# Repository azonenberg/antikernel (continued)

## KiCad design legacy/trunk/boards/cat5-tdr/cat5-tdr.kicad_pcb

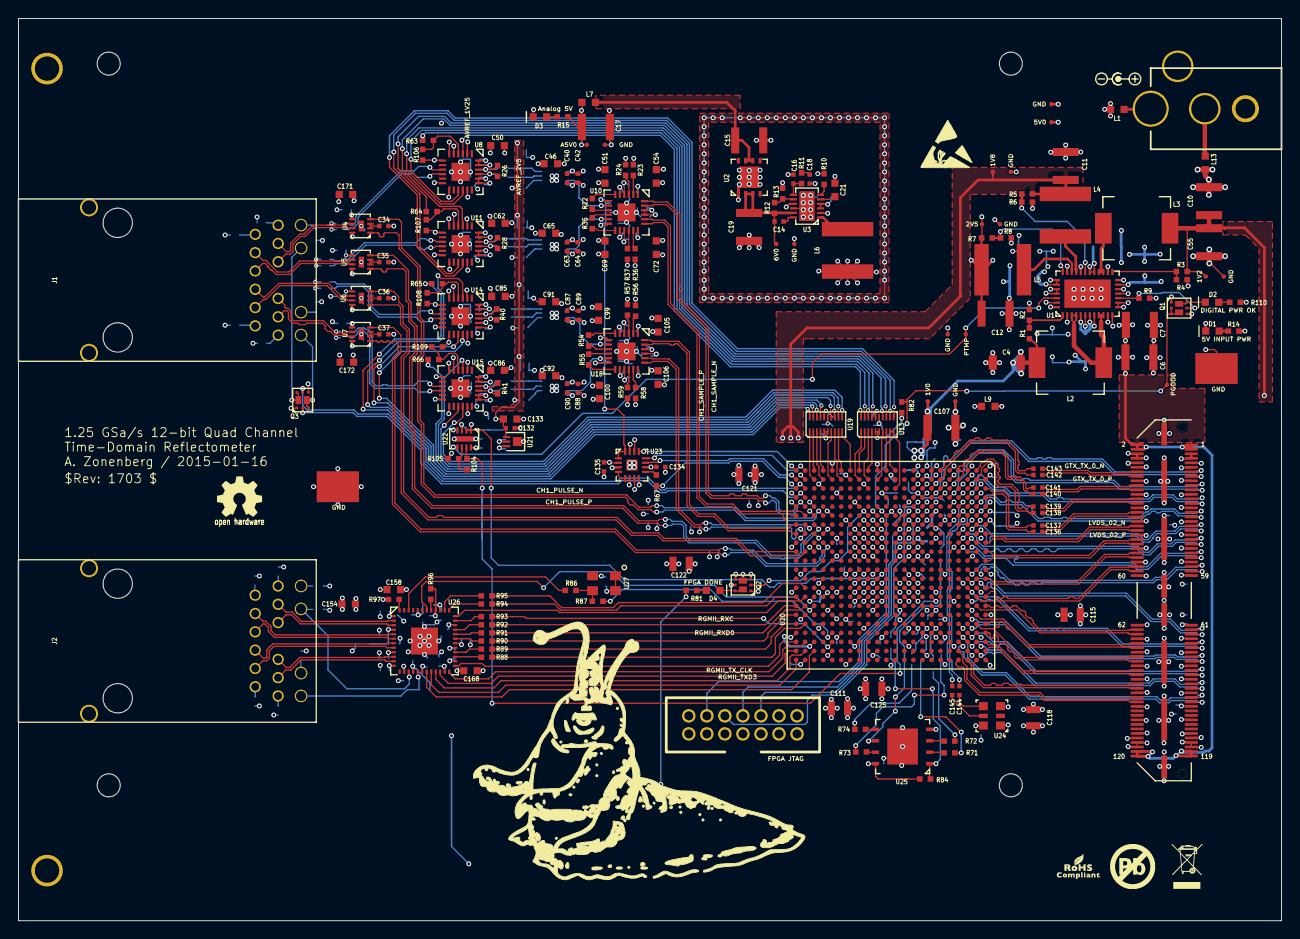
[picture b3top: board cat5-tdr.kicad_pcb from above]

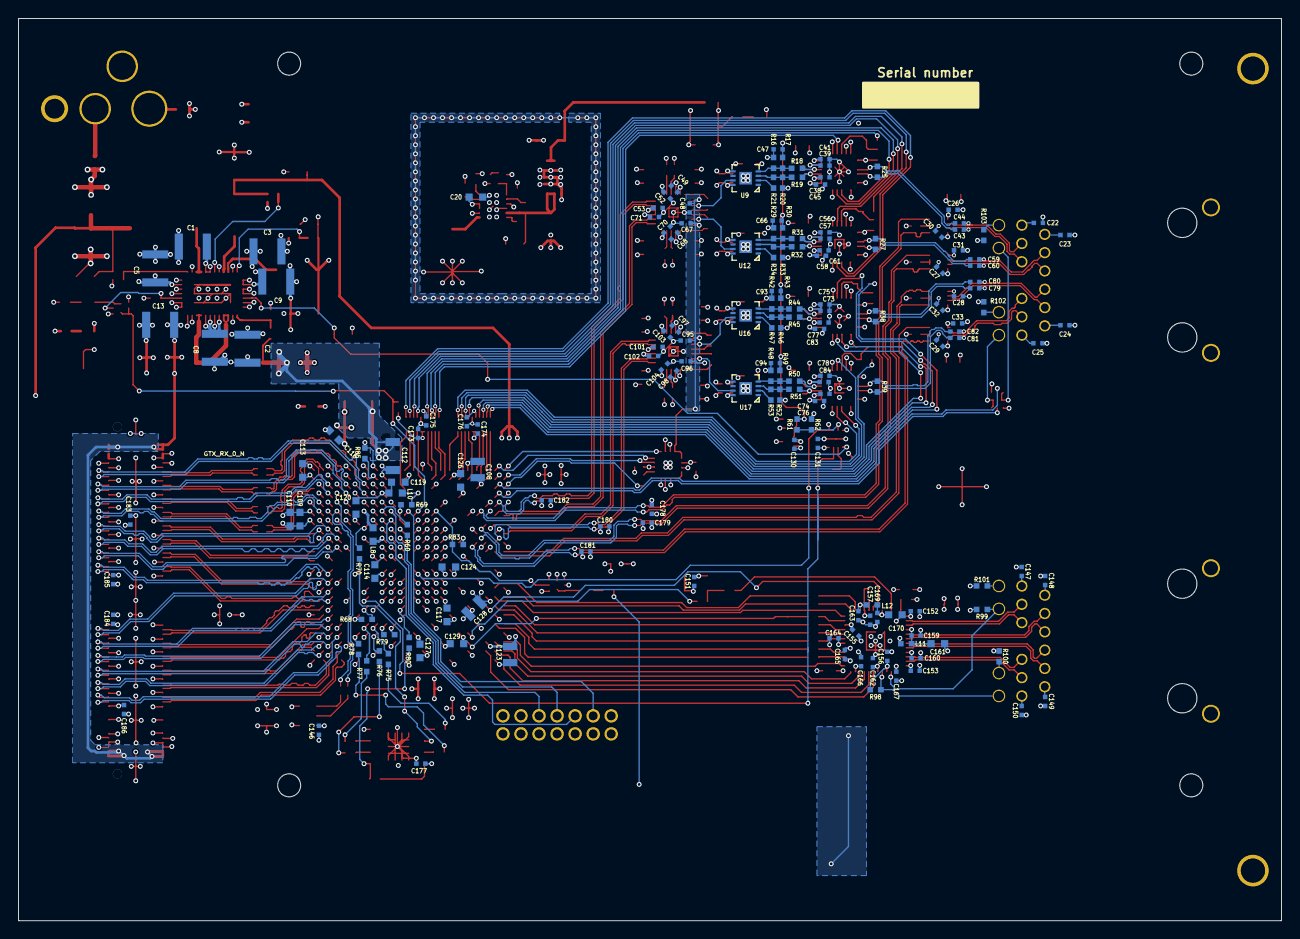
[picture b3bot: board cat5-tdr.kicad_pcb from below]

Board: 4 copper layers, 140.0 x 100.0 mm, 372 parts (174 on the bottom side), 313 nets.

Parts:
C1, C2, C3, C5, C6, C7, C8, C9, C10, C11, C12, C13, C15, C17, C19, C55: 22 uF; EIA_1210_CAP_NOSILK
C4, C112: 100 uF; EIA_1206_CAP_NOSILK
C14, C22, C23, C24, C25, C26, C27, C28, C29, C38, C39, C40, C41, C42, C43, C44, C45, C47, C48, C49, C52, C53, C56, C57, C58, C59, C60, C61, C63, C64, C66, C67, C68, C70, C71, C73, C74, C75, C76, C77, C78, C79, C80, C81, C82, C83, C84, C87, C88, C89, C90, C93, C94, C95, C96, C97, C98, C101, C102, C103, C104, C130, C131, C132, C134, C135, C136, C137, C138, C139, C140, C141, C142, C143, C144, C145, C146, C147, C148, C149, C150, C151, C152, C153, C155, C156, C157, C159, C160, C162, C163, C164, C165, C166, C167, C169, C173, C174, C175, C176, C177, C178, C179, C180, C181, C182, C183, C184, C185, C186: 0.1 uF; EIA_0402_CAP_NOSILK
C16: 10 pF; EIA_0402_CAP_NOSILK
C18: 390 pF; EIA_0402_CAP_NOSILK
C20, C21, C46, C50, C51, C54, C62, C65, C69, C72, C85, C86, C91, C92, C99, C100, C105, C106, C109, C110, C113, C114, C116, C117, C119, C120, C124, C126, C127, C129, C133, C154, C158, C161, C168, C170, C171, C172: 4.7 uF; EIA_0603_CAP_NOSILK
C30, C31, C32, C33, C34, C35, C36, C37: 10 nF; EIA_0402_CAP_NOSILK
C107: 330 uF; EIA_1210_CAP_NOSILK
C108, C111, C115, C118, C121, C122, C123, C125, C128: 47 uF; EIA_0805_CAP_NOSILK
D1, D2, D3, D4: GREEN; EIA_0603_LED
J1, J2: BEL_FUSE_0826-1G1T-23-F; CONN_BELFUSE_0826_1G1T_23_F
J3: XILINX_JTAG; XILINX_JTAG_PTH_MOLEX_0878311420
J4: QTH_060_01_L_D_A_ZMCPINOUT; CONN_SAMTEC_QTH-060-01-L-D-A
K1: BARREL_JACK; CONN_CUI_PJ-058BH_HIPWR_BARREL_NOSLOT
L1, L7, L8, L9, L10, L13: TDK MPZ1608S101ATAH0; EIA_0603_INDUCTOR_NOSILK
L2, L3: 2.2 uH 8.2A; INDUCTOR_TDK_SPM6530
L4, L5: 2.2 uH 3.7A; INDUCTOR_YUDEN_NR6028
L6: 3 uH 3.2A; INDUCTOR_YUDEN_NR6028
L11, L12: 600R; EIA_0402_RES_NOSILK
MECHANICAL_EUROCARD_3U_FRONTHOLES: VAL**; MECHANICAL_EUROCARD_3U_FRONTHOLES
Q1, Q2, Q3: SSM6N58NU; DFN_6_0.65MM_2x2MM_GDS
R1: 255K; EIA_0402_RES_NOSILK
R2, R7: 1.02M; EIA_0402_RES_NOSILK
R3: 232K; EIA_0402_RES_NOSILK
R4: 464K; EIA_0402_RES_NOSILK
R5: 806K; EIA_0402_RES_NOSILK
R6: 649K; EIA_0402_RES_NOSILK
R8: 475K; EIA_0402_RES_NOSILK
R9, R79, R96, R99: 1K; EIA_0402_RES_NOSILK
R10: 28.7K; EIA_0402_RES_NOSILK
R11: 210K; EIA_0402_RES_NOSILK
R12: 820K; EIA_0402_RES_NOSILK
R13: 205K; EIA_0402_RES_NOSILK
R14, R15, R110: 470; EIA_0402_RES_NOSILK
R16, R17, R18, R19, R20, R21, R23, R24, R29, R30, R31, R32, R33, R34, R36, R37, R42, R43, R44, R45, R46, R47, R48, R49, R50, R51, R52, R53, R56, R57, R58, R59, R61, R62, R105: 100K; EIA_0402_RES_NOSILK
R22, R35, R54, R55: 20K; EIA_0402_RES_NOSILK
R25, R26, R27, R28, R38, R39, R40, R41: 100; EIA_0402_RES_NOSILK
R60, R63, R64, R65, R66, R67, R70, R71, R72, R73, R74, R75, R76, R77, R78, R80, R86, R87, R88, R89, R90, R91, R92, R93, R94, R95: 49.9; EIA_0402_RES_NOSILK
R68: 0; EIA_0402_RES_NOSILK
R69, R82: 4.7K; EIA_0402_RES_NOSILK
R81, R100, R101, R102, R103: 220; EIA_0402_RES_NOSILK
R83: 330; EIA_0402_RES_NOSILK
R84: 2.4K; EIA_0402_RES_NOSILK
R85: 100R 1%; EIA_0402_RES_NOSILK
R97: 12.1K 1%; EIA_0402_RES_NOSILK
R98: 10K; EIA_0402_RES_NOSILK
R104: 200K; EIA_0402_RES_NOSILK
R106, R107, R108, R109: 240; EIA_0402_RES_NOSILK
STENCIL8_TOOLING_HOLE, STENCIL8_TOOLING_HOLE#2, STENCIL8_TOOLING_HOLE#3, STENCIL8_TOOLING_HOLE#4: VAL**; STENCIL8_TOOLING_HOLE
TP1, TP2, TP3, TP4, TP5, TP6, TP7, TP8, TP9, TP10, TP11, TP12, TP13, TP14, TP15, TP16, TP17: CONN_1; TESTPOINT_SMT_0.5MM
TP18, TP19: CONN_1; TESTPOINT_SMT_KEYSTONE_5016
U1: LTC3374-QFN; QFN_38_0.5MM_5x7MM
U2: NCP59150MN50; DFN_8_0.8MM_4x4MM
U3: LTC3122; DFN_12_0.5MM_3x4MM
U4, U5, U6, U7: SY58603U; DFN_8_0.5MM_2x2MM
U8, U11, U14, U15: LMH6881; QFN_24_0.5MM_4x4MM
U9, U12, U16, U17: AD8045; DFN_8_0.5MM_3x3MM
U10, U18: LMH7322; QFN_24_0.5MM_4x4MM
U13, U19: TXB0108DQS; DFN_20_0.4MM_2x4MM
U20: XC7K70T-1FBG484; BGA_484_22x22_FULLARRAY_1MM
U21: LT6660 2.5V; DFN_3_0.5MM_2x2MM
U22: MCP6402-DFN; DFN_8_0.5MM_2x3MM
U23: DAC7752; QFN_16_0.5MM_3x3MM
U24: 125 MHz; OSCILLATOR_LVDS_3.2x2.5
U25: MX25U6435FZNI-10G; DFN_8_1.27MM_6x5MM
U26: KSZ9031RN; QFN_48_0.5MM_7x7MM
U27: 25 MHz; OSCILLATOR_3.2x2.5

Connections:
/Analog Front End/1V8: C11.1, C108.1, C111.1, C121.1, C122.1, C123.1, C124.1, C125.1, C126.1, C127.1, C128.1, C129.1, C134.2, C151.1, C155.1, C156.1, C157.1, C158.1, C173.1, C174.1, C177.2, C178.1, C179.1, C180.1, C181.1, C182.1, J3.2, L4.1, L10.2, R5.1, R69.1, R82.2, R83.2, R84.1, R96.1, R98.1, TP7.1, U13.5, U13.6, U19.5, U19.6, U20.AA7, U20.AA17, U20.AB4, U20.AB14, U20.F22, U20.G19, U20.H7, U20.J7, U20.K10, U20.K12, U20.K20, U20.L17, U20.M4, U20.M10, U20.N1, U20.N7, U20.N21, U20.P7, U20.P8, U20.P10, U20.P12, U20.P18, U20.R5, U20.R9, U20.R11, U20.T2, U20.T12, U20.T22, U20.U9, U20.U19, U20.V6, U20.V16, U20.W3, U20.W13, U20.Y10, U20.Y20, U23.7, U23.10, U23.14, U25.8, U26.16, U26.34, U26.40, U27.1, U27.4
/Analog Front End/2V5: C12.1, C26.1, C27.1, C28.1, C29.1, C30.1, C31.1, C32.1, C33.1, C52.1, C53.1, C54.1, C70.1, C71.1, C72.1, C101.1, C102.1, C103.1, C104.1, C105.1, C106.1, C115.1, C118.1, C146.1, C152.1, C153.1, C154.1, C171.1, C172.1, C175.1, C176.1, C183.1, C184.1, C185.1, C186.1, J4.9, J4.10, J4.111, J4.112, L5.1, R7.1, R24.1, R37.1, R57.1, R59.1, R81.1, R100.2, R101.2, R102.1, R103.1, TP9.1, U4.8, U5.8, U6.8, U7.8, U10.1, U10.18, U10.21, U10.22, U13.16, U18.1, U18.18, U18.21, U18.22, U19.16, U20.A17, U20.B14, U20.C11, U20.C21, U20.D8, U20.D18, U20.E15, U20.F12, U20.G9, U20.H16, U24.1, U24.6, U26.1, U26.12
/Analog Front End/A5V0: C17.1, C38.1, C39.1, C40.1, C41.1, C42.1, C45.1, C46.1, C49.1, C50.1, C51.1, C56.1, C57.1, C58.1, C61.1, C62.1, C63.1, C64.1, C65.1, C68.1, C69.1, C73.1, C74.1, C75.1, C76.1, C77.1, C78.1, C83.1, C84.1, C85.1, C86.1, C87.1, C88.1, C89.1, C90.1, C91.1, C92.1, C97.1, C98.1, C99.1, C100.1, C130.1, C131.1, C135.2, L7.1, R15.2, TP13.1, U8.5, U8.19, U8.20, U8.23, U8.24, U9.8, U10.5, U10.14, U11.5, U11.19, U11.20, U11.23, U11.24, U12.8, U14.5, U14.19, U14.20, U14.23, U14.24, U15.5, U15.19, U15.20, U15.23, U15.24, U16.8, U17.8, U18.5, U18.14, U21.3, U22.8, U23.2, U23.6, U23.15
/Analog Front End/AFE_VREF: C48.1, C67.1, C95.1, C96.1, U10.7, U10.12, U18.7, U18.12, U23.1, U23.16
/Analog Front End/AVREF_1V25: U8.2, U11.2, U14.2, U15.2, U20.M12, U22.1, U22.2
/Analog Front End/AVREF_1V25_UNBUF: R61.2, R62.1, U22.3
/Analog Front End/AVREF_2V5: C47.1, C66.1, C93.1, C94.1, C132.1, C133.1, R17.2, R30.2, R43.2, R49.2, R61.1, U21.1
/Analog Front End/CAT5_CH1_N: C44.1, J1.11, U4.6
/Analog Front End/CAT5_CH1_P: C43.1, J1.10, U4.7
/Analog Front End/CAT5_CH2_N: C60.1, J1.5, U5.6
/Analog Front End/CAT5_CH2_P: C59.1, J1.4, U5.7
/Analog Front End/CAT5_CH3_N: C80.1, J1.3, U6.6
/Analog Front End/CAT5_CH3_P: C79.1, J1.2, U6.7
/Analog Front End/CAT5_CH4_N: C82.1, J1.9, U7.6
/Analog Front End/CAT5_CH4_P: C81.1, J1.8, U7.7
/Analog Front End/CH1_AC_N: C44.2, R25.2, U8.9
/Analog Front End/CH1_AC_P: C43.2, R25.1, U8.10
/Analog Front End/CH1_BUF_N: R19.2, R26.2, U8.21
/Analog Front End/CH1_BUF_P: R18.2, R26.1, U8.22
/Analog Front End/CH1_SAMPLE_N: U10.24, U20.AB5
/Analog Front End/CH1_SAMPLE_P: U10.23, U20.AA5
/Analog Front End/CH1_SPI_CS_N: U8.16, U13.17
/Analog Front End/CH1_SPI_MISO: R63.2, R106.2, U8.4
/Analog Front End/CH1_SPI_MOSI: U8.3, U13.20
/Analog Front End/CH1_SPI_SCK: U8.15, U13.18
/Analog Front End/CH1_VDIFF: U9.7, U10.8
/Analog Front End/CH2_AC_N: C60.2, R27.2, U11.9
/Analog Front End/CH2_AC_P: C59.2, R27.1, U11.10
/Analog Front End/CH2_BUF_N: R28.2, R32.2, U11.21
/Analog Front End/CH2_BUF_P: R28.1, R31.2, U11.22
/Analog Front End/CH2_SAMPLE_N: U10.19, U20.AB6
/Analog Front End/CH2_SAMPLE_P: U10.20, U20.AA6
/Analog Front End/CH2_SPI_CS_N: U11.16, U13.11
/Analog Front End/CH2_SPI_MISO: R64.2, R107.2, U11.4
/Analog Front End/CH2_SPI_MOSI: U11.3, U13.14
/Analog Front End/CH2_SPI_SCK: U11.15, U13.12
/Analog Front End/CH2_VDIFF: U10.11, U12.7
/Analog Front End/CH3_AC_N: C80.2, R38.2, U14.9
/Analog Front End/CH3_AC_P: C79.2, R38.1, U14.10
/Analog Front End/CH3_BUF_N: R40.2, R45.2, U14.21
/Analog Front End/CH3_BUF_P: R40.1, R44.2, U14.22
/Analog Front End/CH3_SAMPLE_N: U18.24, U20.AB7
/Analog Front End/CH3_SAMPLE_P: U18.23, U20.AB8
/Analog Front End/CH3_SPI_CS_N: U14.16, U19.17
/Analog Front End/CH3_SPI_MISO: R65.2, R108.2, U14.4
/Analog Front End/CH3_SPI_MOSI: U14.3, U19.19
/Analog Front End/CH3_SPI_SCK: U14.15, U19.18
/Analog Front End/CH3_VDIFF: U16.7, U18.8
/Analog Front End/CH4_AC_N: C82.2, R39.2, U15.9
/Analog Front End/CH4_AC_P: C81.2, R39.1, U15.10
/Analog Front End/CH4_BUF_N: R41.2, R51.2, U15.21
/Analog Front End/CH4_BUF_P: R41.1, R50.2, U15.22
/Analog Front End/CH4_SAMPLE_N: U18.19, U20.AA8
/Analog Front End/CH4_SAMPLE_P: U18.20, U20.AA9
/Analog Front End/CH4_SPI_CS_N: U15.16, U19.11
/Analog Front End/CH4_SPI_MISO: R66.2, R109.2, U15.4
/Analog Front End/CH4_SPI_MOSI: U15.3, U19.13
/Analog Front End/CH4_SPI_SCK: U15.15, U19.12
/Analog Front End/CH4_VDIFF: U17.7, U18.11
/Analog Front End/DAC_SPI_CS_N: U20.AB2, U23.11
/Analog Front End/DAC_SPI_MISO: R67.2, U23.9
/Analog Front End/DAC_SPI_MOSI: U20.AB1, U23.13
/Analog Front End/DAC_SPI_SCK: U20.AA1, U23.12
/Analog Front End/GND: C1.2, C2.2, C3.2, C4.2, C5.2, C6.2, C7.2, C8.2, C9.2, C10.2, C11.2, C12.2, C13.2, C15.2, C16.2, C17.2, C18.2, C19.2, C20.2, C21.2, C22.2, C23.2, C24.2, C25.2, C26.2, C27.2, C28.2, C29.2, C30.2, C31.2, C32.2, C33.2, C34.2, C35.2, C36.2, C37.2, C38.2, C39.2, C40.2, C41.2, C42.2, C45.2, C46.2, C47.2, C48.2, C49.2, C50.2, C51.2, C52.2, C53.2, C54.2, C55.2, C56.2, C57.2, C58.2, C61.2, C62.2, C63.2, C64.2, C65.2, C66.2, C67.2, C68.2, C69.2, C70.2, C71.2, C72.2, C73.2, C74.2, C75.2, C76.2, C77.2, C78.2, C83.2, C84.2, C85.2, C86.2, C87.2, C88.2, C89.2, C90.2, C91.2, C92.2, C93.2, C94.2, C95.2, C96.2, C97.2, C98.2, C99.2, C100.2, C101.2, C102.2, C103.2, C104.2, C105.2, C106.2, C107.2, C108.2, C109.2, C110.2, C111.2, C112.2, C113.2, C114.2, C115.2, C116.2, C117.2, C118.2, C119.2, C120.2, C121.2, C122.2, C123.2, C124.2, C125.2, C126.2, C127.2, C128.2, C129.2, C130.2, C131.2, C132.2, C133.2, C134.1, C135.1, C146.2, C147.2, C148.2, C149.2, C150.2, C151.2, C152.2, C153.2, C154.2, C155.2, C156.2, C157.2, C158.2, C159.2, C160.2, C161.2, C162.2, C163.2, C164.2, C165.2, C166.2, C167.2, C168.2, C169.2, C170.2, C171.2, C172.2, C173.2, C174.2, C175.2, C176.2, C177.1, C178.2, C179.2, C180.2, C181.2, C182.2, C183.2, C184.2, C185.2, C186.2, D1.2, D3.2, J1.17, J2.17, J3.3, J3.5, J3.7, J3.9, J3.11, J4.5, J4.6, J4.7, J4.8, J4.11, J4.12, J4.17, J4.18, J4.23, J4.24, J4.29, J4.30, J4.35, J4.36, J4.41, J4.42, J4.47, J4.48, J4.53, J4.54, J4.59, J4.60, J4.61, J4.62, J4.67, J4.68, J4.73, J4.74, J4.79, J4.80, J4.85, J4.86, J4.91, J4.92, J4.97, J4.98, J4.103, J4.104, J4.109, J4.110, J4.113, J4.114, J4.115, J4.116, J4.121, J4.122, J4.123, J4.124, J4.125, J4.126, J4.127, J4.128, L13.1, Q1.S1, Q1.S2, Q2.D2, Q2.G2, Q2.S1, Q2.S2, Q3.S1, Q3.S2, R2.1, R4.1, R6.1, R8.1, R10.1, R13.1, R16.2, R20.2, R23.1, R29.2, R33.2, R36.1, R42.2, R46.2, R48.2, R52.2, R56.1, R58.1, R62.2, R68.2, R79.2, R97.1, R99.1, R105.1, R106.1, R107.1, R108.1, R109.1, TP1.1, TP4.1, TP6.1, TP8.1, TP10.1, TP11.1, TP14.1, TP16.1, TP18.1, TP19.1, U1.13, U1.14, U1.16, U1.18, U1.37, U1.PAD, U2.1, U2.PAD, U3.2, U3.10, U3.PAD, U4.5, U4.PAD, U5.5, U5.PAD, U6.5, U6.PAD, U7.5, U7.PAD, U8.6, U8.7, U8.12, U8.13, U8.17, U8.PAD, U9.5, U9.PAD, U10.4, U10.15, U10.PAD, U11.6, U11.7, U11.12, U11.13, U11.17, U11.PAD, U12.5, U12.PAD, U13.15, U14.6, U14.7, U14.12, U14.13, U14.17, U14.PAD, U15.6, U15.7, U15.12, U15.13, U15.17, U15.PAD, U16.5, U16.PAD, U17.5, U17.PAD, U18.4, U18.15, U18.PAD, U19.15, U20.A1, U20.A5, U20.A7, U20.A12, U20.A22, U20.AA2, U20.AA12, U20.AA22, U20.AB9, U20.AB19, U20.B3, U20.B4, U20.B7, U20.B9, U20.B19, U20.C1, U20.C5, U20.C7, U20.C16, U20.D3, U20.D4, U20.D7, U20.D13, U20.E1, U20.E5, U20.E7, U20.E10, U20.E20, U20.F3, U20.F4, U20.F7, U20.F17, U20.G1, U20.G5, U20.G14, U20.H3, U20.H4, U20.H5, U20.H6, U20.H11, U20.H21, U20.J1, U20.J2, U20.J3, U20.J5, U20.J8, U20.J10, U20.J12, U20.J14, U20.J18, U20.K5, U20.K9, U20.K11, U20.K13, U20.K15, U20.L2, U20.L8, U20.L10, U20.L11, U20.L14, U20.L22, U20.M7, U20.M9, U20.M13, U20.M15, U20.M19, U20.N6, U20.N8, U20.N10, U20.N11, U20.N12, U20.N14, U20.N16, U20.P3, U20.P9, U20.P11, U20.P13, U20.P15, U20.R8, U20.R10, U20.R12, U20.R14, U20.R20, U20.T7, U20.T17, U20.U4, U20.U14, U20.V1, U20.V11, U20.V21, U20.W8, U20.W18, U20.Y5, U20.Y15, U21.2, U21.PAD, U22.4, U22.PAD, U23.3, U23.8, U23.PAD, U24.3, U25.4, U25.PAD, U26.29, U26.PAD, U27.2
/Analog Front End/PTMP_BUF: R104.2, U20.G15, U22.7
/Analog Front End/PTMP_FB: R104.1, R105.2, U22.6
/Analog Front End/UNUSED_DACOUT: U23.4, U23.5
/Boot Flash/FLASH_SPI_CS_N: R80.2, R84.2, U25.1
/Boot Flash/FLASH_SPI_DQ0: R74.1, R75.2
/Boot Flash/FLASH_SPI_DQ1: R71.2, R76.2
/Boot Flash/FLASH_SPI_DQ2: R72.2, R77.2
/Boot Flash/FLASH_SPI_DQ3: R73.1, R78.2
/Ethernet interface/1V2: C10.1, C55.1, C162.1, C163.1, C164.1, C165.1, C166.1, C167.1, C168.1, L3.1, L9.2, L11.2, L12.2, R3.1, TP5.1, U26.14, U26.18, U26.23, U26.26, U26.30, U26.39
/Ethernet interface/A1V2_ETH: C159.1, C160.1, C161.1, L11.1, U26.4, U26.9
/Ethernet interface/A1V2_ETHPLL: C169.1, C170.1, L12.1, U26.44
/Ethernet interface/CH1_TAP: C147.1, J2.12
/Ethernet interface/CH2_TAP: C148.1, J2.6
/Ethernet interface/CH3_TAP: C149.1, J2.1
/Ethernet interface/CH4_TAP: C150.1, J2.7
/Ethernet interface/CLK_25MHZ_RAW: R86.2, R87.2, U27.3
/Ethernet interface/ETH_4_N: J2.9, U26.10
/Ethernet interface/ETH_4_P: J2.8, U26.11
/Ethernet interface/ETH_A_N: J2.10, U26.3
/Ethernet interface/ETH_A_P: J2.11, U26.2
/Ethernet interface/ETH_B_N: J2.5, U26.5
/Ethernet interface/ETH_B_P: J2.4, U26.6
/Ethernet interface/ETH_C_N: J2.2, U26.8
/Ethernet interface/ETH_C_P: J2.3, U26.7
/Ethernet interface/ETH_LED1_N: J2.13, R98.2, U26.17
/Ethernet interface/ETH_LED1_P: J2.14, R100.1
/Ethernet interface/ETH_LED2_N: J2.15, R99.2, U26.15
/Ethernet interface/ETH_LED2_P: J2.16, R101.1
/Ethernet interface/ETH_RESET_N: U20.Y16, U26.42
/Ethernet interface/FPGA_CLK_25MHZ: R87.1, U20.V19
/Ethernet interface/PHY_CLK_25MHZ: R86.1, U26.46
/Ethernet interface/PHY_INT_N: R95.1, U20.AA14
/Ethernet interface/PHY_MDC: U20.AA15, U26.36
/Ethernet interface/PHY_MDIO: R94.1, U20.AB15
/Ethernet interface/RBIAS_ETH: R97.2, U26.48
/Ethernet interface/RGMII_RXC: R93.1, U20.V20
/Ethernet interface/RGMII_RXD0: R91.1, U20.AA16
/Ethernet interface/RGMII_RXD1: R90.1, U20.AB17
/Ethernet interface/RGMII_RXD2: R89.1, U20.AB18
/Ethernet interface/RGMII_RXD3: R88.1, U20.AA18
/Ethernet interface/RGMII_RX_DV: R92.1, U20.AB16
/Ethernet interface/RGMII_TXD0: U20.Y21, U26.19
/Ethernet interface/RGMII_TXD1: U20.AB22, U26.20
/Ethernet interface/RGMII_TXD2: U20.AA21, U26.21
/Ethernet interface/RGMII_TXD3: U20.AB21, U26.22
/Ethernet interface/RGMII_TX_CLK: U20.AA20, U26.24
/Ethernet interface/RGMII_TX_EN: U20.AB20, U26.25
/FPGA Support/1V0: C4.1, C107.1, C112.1, C114.1, C117.1, L2.1, L8.2, R1.1, TP3.1, U20.J9, U20.J11, U20.J13, U20.J15, U20.K8, U20.K14, U20.L9, U20.L13, U20.L15, U20.M8, U20.M14, U20.N9, U20.N13, U20.N15, U20.P14, U20.R13, U20.R15
/FPGA Support/CCLK: R70.2, U25.6
/FPGA Support/CCLK_UNTERM: R70.1, U20.G7
/FPGA Support/FPGA_DONE: Q2.G1, R83.1, U20.P6
/FPGA Support/GTX_VAUX: C119.1, C120.1, L10.1, U20.J4
/FPGA Support/GTX_VCC: C109.1, C110.1, L8.1, U20.A6, U20.C6, U20.E6, U20.G6
/FPGA Support/GTX_VTT: C113.1, C116.1, L9.1, R85.2, U20.A2, U20.C2, U20.E2, U20.G2, U20.H1
/FPGA Support/INIT_B: R69.2, U20.L7
/FPGA Support/JTAG_TCK: J3.6, U20.K7
/FPGA Support/JTAG_TDI: J3.10, U20.K6
/FPGA Support/JTAG_TDO: R60.1, U20.J6
/FPGA Support/JTAG_TDO_TERM: J3.8, R60.2
/FPGA Support/JTAG_TMS: J3.4, U20.L6
/FPGA pulse handling/CH1_PULSE_N: U4.4, U20.Y6
/FPGA pulse handling/CH1_PULSE_P: U4.1, U20.W6
/FPGA pulse handling/CH1_SPI_CS_N_1V8: U13.4, U20.P1
/FPGA pulse handling/CH1_SPI_MISO_1V8: U13.2, U20.R1
/FPGA pulse handling/CH1_SPI_MOSI_1V8: U13.1, U20.R2
/FPGA pulse handling/CH1_SPI_SCK_1V8: U13.3, U20.P2
/FPGA pulse handling/CH2_PULSE_N: U5.4, U20.Y7
/FPGA pulse handling/CH2_PULSE_P: U5.1, U20.Y8
/FPGA pulse handling/CH2_SPI_CS_N_1V8: U13.10, U20.L3
/FPGA pulse handling/CH2_SPI_MISO_1V8: U13.8, U20.M1
/FPGA pulse handling/CH2_SPI_MOSI_1V8: U13.7, U20.N2
/FPGA pulse handling/CH2_SPI_SCK_1V8: U13.9, U20.L1
/FPGA pulse handling/CH3_PULSE_N: U6.4, U20.AB10
/FPGA pulse handling/CH3_PULSE_P: U6.1, U20.AA10
/FPGA pulse handling/CH3_SPI_CS_N_1V8: U19.4, U20.W1
/FPGA pulse handling/CH3_SPI_MISO_1V8: U19.1, U20.Y2
/FPGA pulse handling/CH3_SPI_MOSI_1V8: U19.2, U20.Y1
/FPGA pulse handling/CH3_SPI_SCK_1V8: U19.3, U20.W2
/FPGA pulse handling/CH4_PULSE_N: U7.4, U20.Y9
/FPGA pulse handling/CH4_PULSE_P: U7.1, U20.W9
/FPGA pulse handling/CH4_SPI_CS_N_1V8: U19.10, U20.T1
/FPGA pulse handling/CH4_SPI_MISO_1V8: U19.7, U20.V2
/FPGA pulse handling/CH4_SPI_MOSI_1V8: U19.8, U20.U2
/FPGA pulse handling/CH4_SPI_SCK_1V8: U19.9, U20.U1
/FPGA pulse handling/DAC_SPI_MISO_TERM: R67.1, U20.AB3
/FPGA pulse handling/TDR_LED1: Q3.G2, U20.AA3
/FPGA pulse handling/TDR_LED2: Q3.G1, U20.AA4
/GPIO header/5V0: C1.1, C2.1, C3.1, C5.1, C6.1, C7.1, C8.1, C9.1, C13.1, C20.1, J4.1, J4.2, J4.3, J4.4, J4.117, J4.118, J4.119, J4.120, L1.1, L6.2, R9.2, R14.2, R110.2, TP2.1, U1.2, U1.5, U1.6, U1.7, U1.8, U1.11, U1.12, U1.17, U1.19, U1.21, U1.24, U1.25, U1.27, U1.30, U1.32, U1.33, U1.34, U1.35, U1.38, U3.3, U3.4, U3.9
/GPIO header/G0TD_N: C143.2, U20.F1
/GPIO header/G0TD_P: C142.2, U20.F2
/GPIO header/G1TD_N: C141.2, U20.D1
/GPIO header/G1TD_P: C140.2, U20.D2
/GPIO header/G2TD_N: C139.2, U20.B1
/GPIO header/G2TD_P: C138.2, U20.B2
/GPIO header/G3TD_N: C137.2, U20.A3
/GPIO header/G3TD_P: C136.2, U20.A4
/GPIO header/GREF0_N: C145.2, U20.D5
/GPIO header/GREF0_P: C144.2, U20.D6
/GPIO header/GTX_REFCLK_0_N: C145.1, U24.5
/GPIO header/GTX_REFCLK_0_P: C144.1, U24.4
/GPIO header/GTX_RREF: R85.1, U20.H2
/GPIO header/GTX_RX_0_N: J4.13, U20.G3
/GPIO header/GTX_RX_0_P: J4.15, U20.G4
/GPIO header/GTX_RX_1_N: J4.19, U20.E3
/GPIO header/GTX_RX_1_P: J4.21, U20.E4
/GPIO header/GTX_RX_2_N: J4.25, U20.C3
/GPIO header/GTX_RX_2_P: J4.27, U20.C4
/GPIO header/GTX_RX_3_N: J4.31, U20.B5
/GPIO header/GTX_RX_3_P: J4.33, U20.B6
/GPIO header/GTX_TX_0_N: C143.1, J4.14
/GPIO header/GTX_TX_0_P: C142.1, J4.16
/GPIO header/GTX_TX_1_N: C141.1, J4.20
/GPIO header/GTX_TX_1_P: C140.1, J4.22
/GPIO header/GTX_TX_2_N: C139.1, J4.26
/GPIO header/GTX_TX_2_P: C138.1, J4.28
/GPIO header/GTX_TX_3_N: C137.1, J4.32
/GPIO header/GTX_TX_3_P: C136.1, J4.34
/GPIO header/LVDS_01_N: J4.39, U20.B8
/GPIO header/LVDS_01_P: J4.37, U20.C8
/GPIO header/LVDS_02_N: J4.38, U20.A8
/GPIO header/LVDS_02_P: J4.40, U20.A9
/GPIO header/LVDS_03_N: J4.45, U20.C9
/GPIO header/LVDS_03_P: J4.43, U20.D9
/GPIO header/LVDS_04_N: J4.44, U20.A10
/GPIO header/LVDS_04_P: J4.46, U20.A11
/GPIO header/LVDS_05_N: J4.49, U20.C10
/GPIO header/LVDS_05_P: J4.51, U20.D10
/GPIO header/LVDS_06_N: J4.52, U20.A14
/GPIO header/LVDS_06_P: J4.50, U20.A13
/GPIO header/LVDS_07_N: J4.57, U20.B12
/GPIO header/LVDS_07_P: J4.55, U20.C12
/GPIO header/LVDS_08_N: J4.56, U20.A15
/GPIO header/LVDS_08_P: J4.58, U20.B15
/GPIO header/LVDS_09_N: J4.65, U20.B13
/GPIO header/LVDS_09_P: J4.63, U20.C13
/GPIO header/LVDS_10_N: J4.64, U20.A16
/GPIO header/LVDS_10_P: J4.66, U20.B16
/GPIO header/LVDS_11_N: J4.71, U20.C15
/GPIO header/LVDS_11_P: J4.69, U20.C14
/GPIO header/LVDS_12_N: J4.72, U20.A18
/GPIO header/LVDS_12_P: J4.70, U20.B17
/GPIO header/LVDS_13_N: J4.77, U20.C18
/GPIO header/LVDS_13_P: J4.75, U20.C17
/GPIO header/LVDS_14_N: J4.78, U20.A19
/GPIO header/LVDS_14_P: J4.76, U20.B18
/GPIO header/LVDS_15_N: J4.83, U20.C20
/GPIO header/LVDS_15_P: J4.81, U20.C19
/GPIO header/LVDS_16_N: J4.84, U20.A21
/GPIO header/LVDS_16_P: J4.82, U20.A20
/GPIO header/LVDS_17_N: J4.89, U20.B21
/GPIO header/LVDS_17_P: J4.87, U20.B20
/GPIO header/LVDS_18_N: J4.88, U20.B22
/GPIO header/LVDS_18_P: J4.90, U20.C22
/GPIO header/LVDS_19_N: J4.95, U20.D20
/GPIO header/LVDS_19_P: J4.93, U20.D19
/GPIO header/LVDS_20_N: J4.96, U20.D22
/GPIO header/LVDS_20_P: J4.94, U20.D21
/Power Supply/5V0_IN: K1.1, L1.2
/Power Supply/6V0: C14.1, C19.1, R12.2, TP15.1, U2.2, U2.3, U3.11
/Power Supply/6V0_COMP: C16.1, R11.2, U3.7
/Power Supply/6V0_FB: R12.1, R13.2, U3.8
/Power Supply/A5V0_RAW: C15.1, L7.2, U2.6, U2.7
/Power Supply/FB_1V0: R1.2, R2.2, U1.1
/Power Supply/FB_1V2: R3.2, R4.2, U1.20
/Power Supply/FB_1V8: R5.2, R6.2, U1.26
/Power Supply/FB_2V5: R7.2, R8.2, U1.31
/Power Supply/GND_RAW: K1.2, L13.2
/Power Supply/PGOOD: Q1.D2, Q1.G1, R82.1, TP17.1, U20.M6
/Power Supply/PGOOD_5V0: Q1.G2, R9.1, U1.15
/Power Supply/PSU_TEMP: TP12.1, U1.36, U22.5
/Power Supply/SW_1V0: L2.2, U1.3, U1.4, U1.9, U1.10
/Power Supply/SW_1V2: L3.2, U1.22, U1.23
/Power Supply/SW_1V8: L4.2, U1.28
/Power Supply/SW_2V5: L5.2, U1.29
/Pulse Shaping/CH1_VT: C34.1, U4.2, U4.3
/Pulse Shaping/CH2_VT: C35.1, U5.2, U5.3
/Pulse Shaping/CH3_VT: C36.1, U6.2, U6.3
/Pulse Shaping/CH4_VT: C37.1, U7.2, U7.3
/TDR RJ45 connector/CAT5_CH1_TAP: C22.1, J1.12
/TDR RJ45 connector/CAT5_CH2_TAP: C23.1, J1.6
/TDR RJ45 connector/CAT5_CH3_TAP: C24.1, J1.1
/TDR RJ45 connector/CAT5_CH4_TAP: C25.1, J1.7
/TDR RJ45 connector/TDR_LED1_N: J1.13, Q3.D2
/TDR RJ45 connector/TDR_LED1_P: J1.14, R102.2
/TDR RJ45 connector/TDR_LED2_N: J1.15, Q3.D1
/TDR RJ45 connector/TDR_LED2_P: J1.16, R103.2
unnamed: C14.2, U3.12
unnamed: C18.1, R11.1
unnamed: C21.1, U3.5
unnamed: D1.1, R14.1
unnamed: D2.1, R110.1
unnamed: D2.2, Q1.D1
unnamed: D3.1, R15.1
unnamed: D4.1, R81.2
unnamed: D4.2, Q2.D1
unnamed: L6.1, U3.1
unnamed: R10.2, U3.6
unnamed: R16.1, R17.1, R18.1, U9.4
unnamed: R19.1, R20.1, R21.1, U9.3
unnamed: R21.2, U9.2
unnamed: R22.1, U10.6
unnamed: R22.2, U10.9
unnamed: R23.2, U10.2
unnamed: R24.2, U10.3
unnamed: R29.1, R30.1, R31.1, U12.4
unnamed: R32.1, R33.1, R34.1, U12.3
unnamed: R34.2, U12.2
unnamed: R35.1, U10.13
unnamed: R35.2, U10.10
unnamed: R36.2, U10.17
unnamed: R37.2, U10.16
unnamed: R42.1, R43.1, R44.1, U16.4
unnamed: R45.1, R46.1, R47.1, U16.3
unnamed: R47.2, U16.2
unnamed: R48.1, R49.1, R50.1, U17.4
unnamed: R51.1, R52.1, R53.1, U17.3
unnamed: R53.2, U17.2
unnamed: R54.1, U18.6
unnamed: R54.2, U18.9
unnamed: R55.1, U18.13
unnamed: R55.2, U18.10
unnamed: R56.2, U18.2
unnamed: R57.2, U18.3
unnamed: R58.2, U18.17
unnamed: R59.2, U18.16
unnamed: R63.1, U13.19
unnamed: R64.1, U13.13
unnamed: R65.1, U19.20
unnamed: R66.1, U19.14
unnamed: R68.1, U20.G16
unnamed: R71.1, U25.2
unnamed: R72.1, U25.3
unnamed: R73.2, U25.7
unnamed: R74.2, U25.5
unnamed: R75.1, U20.H18
unnamed: R76.1, U20.H19
unnamed: R77.1, U20.G18
unnamed: R78.1, U20.F19
unnamed: R79.1, U20.K18
unnamed: R80.1, U20.L16
unnamed: R88.2, U26.27
unnamed: R89.2, U26.28
unnamed: R90.2, U26.31
unnamed: R91.2, U26.32
unnamed: R92.2, U26.33
unnamed: R93.2, U26.35
unnamed: R94.2, U26.37
unnamed: R95.2, U26.38
unnamed: R96.2, U26.41

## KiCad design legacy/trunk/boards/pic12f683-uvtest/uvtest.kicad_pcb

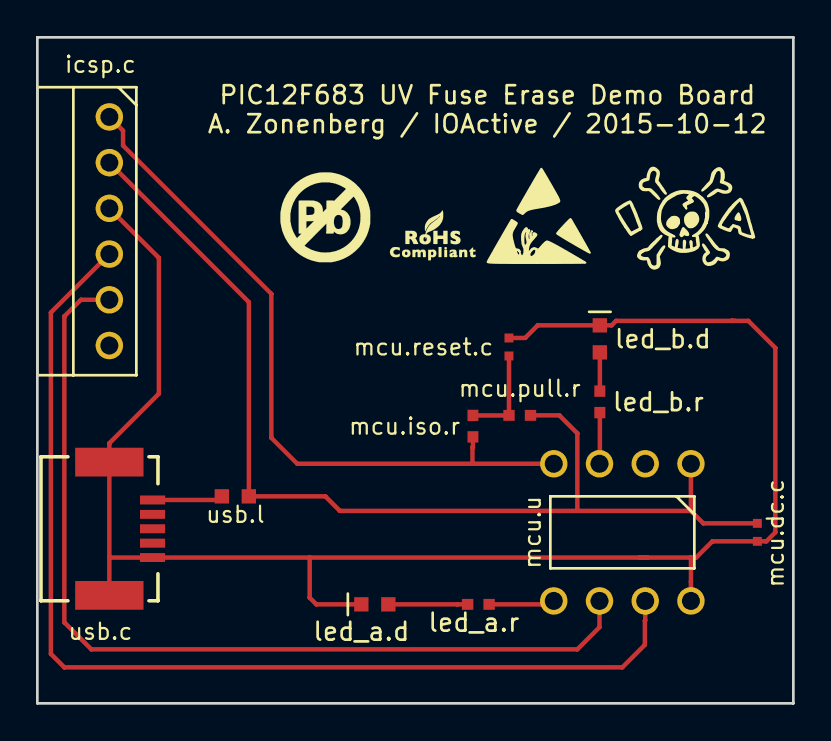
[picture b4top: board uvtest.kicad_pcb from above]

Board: 2 copper layers, 42.0 x 37.0 mm, 12 parts (0 on the bottom side), 11 nets.

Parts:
icsp.c: S1111EC-06-ND; CONN_HEADER_2.54MM_1x6_RA
led_a.d: green; EIA_0603_LED
led_a.r: 470; EIA_0402_RES_NOSILK
led_b.d: green; EIA_0603_LED
led_b.r: 470; EIA_0402_RES_NOSILK
mcu.dc.c, mcu.reset.c: 100nF; EIA_0402_CAP_NOSILK
mcu.iso.r: 470; EIA_0402_RES_NOSILK
mcu.pull.r: 10K; EIA_0402_RES_NOSILK
mcu.u: PIC12F683-I/P; DIP_8_2.54MM_7.62MM
usb.c: UX60SC-MB-5ST(80); CONN_HIROSE_UX60S-MB-5ST_MINI_USB
usb.l: MPZ1608S601ATA00; EIA_0603_INDUCTOR_NOSILK

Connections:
gnd: icsp.c.3, led_a.d.2, led_b.d.2, mcu.dc.c.2, mcu.reset.c.2, mcu.u.8, usb.c.5, usb.c.6, usb.c.7
gpio2: led_a.r.1, mcu.u.5
gpio4: led_b.r.1, mcu.u.3
icsp_mclr: icsp.c.1, mcu.iso.r.2, mcu.u.4
icsp_pgc: icsp.c.5, mcu.u.6
icsp_pgd: icsp.c.4, mcu.u.7
led_a.a: led_a.d.1, led_a.r.2
led_b.a: led_b.d.1, led_b.r.2
mcu.mclr_rc: mcu.iso.r.1, mcu.pull.r.2, mcu.reset.c.1
usb.vbus_internal: usb.c.1, usb.l.1
v5p0: icsp.c.2, mcu.dc.c.1, mcu.pull.r.1, mcu.u.1, usb.l.2

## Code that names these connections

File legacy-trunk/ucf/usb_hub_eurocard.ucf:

########################################################################################################################
# Hub status

NET "hub_status[0]" LOC = P11 | IOSTANDARD = LVCMOS33 | PULLUP;
NET "hub_fault[0]"  LOC = P10 | IOSTANDARD = LVCMOS33 | PULLUP;
NET "hub_status[1]" LOC = P13 | IOSTANDARD = LVCMOS33 | PULLUP;
NET "hub_fault[1]"  LOC = P12 | IOSTANDARD = LVCMOS33 | PULLUP;

########################################################################################################################
# Port status

NET "port_status[0]" LOC = P7  | IOSTANDARD = LVCMOS33 | PULLUP;
NET "port_fault[0]"  LOC = P6  | IOSTANDARD = LVCMOS33 | PULLUP;
NET "port_status[1]" LOC = P9  | IOSTANDARD = LVCMOS33 | PULLUP;
NET "port_fault[1]"  LOC = P8  | IOSTANDARD = LVCMOS33 | PULLUP;
NET "port_status[2]" LOC = P90 | IOSTANDARD = LVCMOS33 | PULLUP;
NET "port_fault[2]"  LOC = P89 | IOSTANDARD = LVCMOS33 | PULLUP;
NET "port_status[3]" LOC = P92 | IOSTANDARD = LVCMOS33 | PULLUP;
NET "port_fault[3]"  LOC = P91 | IOSTANDARD = LVCMOS33 | PULLUP;
NET "port_status[4]" LOC = P94 | IOSTANDARD = LVCMOS33 | PULLUP;
NET "port_fault[4]"  LOC = P93 | IOSTANDARD = LVCMOS33 | PULLUP;
NET "port_status[5]" LOC = P96 | IOSTANDARD = LVCMOS33 | PULLUP;
NET "port_fault[5]"  LOC = P95 | IOSTANDARD = LVCMOS33 | PULLUP;
NET "port_status[6]" LOC = P30 | IOSTANDARD = LVCMOS33 | PULLUP;
NET "port_fault[6]"  LOC = P29 | IOSTANDARD = LVCMOS33 | PULLUP;
NET "port_status[7]" LOC = P33 | IOSTANDARD = LVCMOS33 | PULLUP;
NET "port_fault[7]"  LOC = P32 | IOSTANDARD = LVCMOS33 | PULLUP;
NET "port_status[8]" LOC = P35 | IOSTANDARD = LVCMOS33 | PULLUP;
NET "port_fault[8]"  LOC = P34 | IOSTANDARD = LVCMOS33 | PULLUP;
NET "port_status[9]" LOC = P37 | IOSTANDARD = LVCMOS33 | PULLUP;
NET "port_fault[9]"  LOC = P36 | IOSTANDARD = LVCMOS33 | PULLUP;

########################################################################################################################
# Port power enables from hub controller

NET "port_pwr_n[0]"  LOC = P4  | IOSTANDARD = LVCMOS33 | PULLUP;
NET "port_pwr_n[1]"  LOC = P1  | IOSTANDARD = LVCMOS33 | PULLUP;
NET "port_pwr_n[2]"  LOC = P82 | IOSTANDARD = LVCMOS33 | PULLUP;
NET "port_pwr_n[3]"  LOC = P81 | IOSTANDARD = LVCMOS33 | PULLUP;
NET "port_pwr_n[4]"  LOC = P3  | IOSTANDARD = LVCMOS33 | PULLUP;
NET "port_pwr_n[5]"  LOC = P2  | IOSTANDARD = LVCMOS33 | PULLUP;
NET "port_pwr_n[6]"  LOC = P28 | IOSTANDARD = LVCMOS33 | PULLUP;
NET "port_pwr_n[7]"  LOC = P27 | IOSTANDARD = LVCMOS33 | PULLUP;
NET "port_pwr_n[8]"  LOC = P39 | IOSTANDARD = LVCMOS33 | PULLUP;
NET "port_pwr_n[9]"  LOC = P40 | IOSTANDARD = LVCMOS33 | PULLUP;

########################################################################################################################
# Port power enables to PMIC

NET "vbus_en_n[0]"  LOC = P71  | IOSTANDARD = LVCMOS33;
NET "vbus_en_n[1]"  LOC = P70  | IOSTANDARD = LVCMOS33;
NET "vbus_en_n[2]"  LOC = P77  | IOSTANDARD = LVCMOS33;
NET "vbus_en_n[3]"  LOC = P78  | IOSTANDARD = LVCMOS33;
NET "vbus_en_n[4]"  LOC = P79  | IOSTANDARD = LVCMOS33;
NET "vbus_en_n[5]"  LOC = P80  | IOSTANDARD = LVCMOS33;
NET "vbus_en_n[6]"  LOC = P14  | IOSTANDARD = LVCMOS33;
NET "vbus_en_n[7]"  LOC = P15  | IOSTANDARD = LVCMOS33;
NET "vbus_en_n[8]"  LOC = P16  | IOSTANDARD = LVCMOS33;
NET "vbus_en_n[9]"  LOC = P17  | IOSTANDARD = LVCMOS33;

########################################################################################################################
# Indicator LEDs

NET "status_led_p"  LOC = P42 | IOSTANDARD = LVCMOS33;
NET "status_led_n"  LOC = P41 | IOSTANDARD = LVCMOS33;

NET "port_led_p[0]" LOC = P43 | IOSTANDARD = LVCMOS33;
NET "port_led_p[1]" LOC = P46 | IOSTANDARD = LVCMOS33;
NET "port_led_p[2]" LOC = P50 | IOSTANDARD = LVCMOS33;
NET "port_led_p[3]" LOC = P53 | IOSTANDARD = LVCMOS33;
NET "port_led_p[4]" LOC = P55 | IOSTANDARD = LVCMOS33;
NET "port_led_p[5]" LOC = P58 | IOSTANDARD = LVCMOS33;
NET "port_led_p[6]" LOC = P60 | IOSTANDARD = LVCMOS33;
NET "port_led_p[7]" LOC = P63 | IOSTANDARD = LVCMOS33;
NET "port_led_p[8]" LOC = P65 | IOSTANDARD = LVCMOS33;
NET "port_led_p[9]" LOC = P67 | IOSTANDARD = LVCMOS33;

NET "port_led_n[0]" LOC = P44 | IOSTANDARD = LVCMOS33;
NET "port_led_n[1]" LOC = P49 | IOSTANDARD = LVCMOS33;
NET "port_led_n[2]" LOC = P52 | IOSTANDARD = LVCMOS33;
NET "port_led_n[3]" LOC = P54 | IOSTANDARD = LVCMOS33;
NET "port_led_n[4]" LOC = P56 | IOSTANDARD = LVCMOS33;
NET "port_led_n[5]" LOC = P59 | IOSTANDARD = LVCMOS33;
NET "port_led_n[6]" LOC = P61 | IOSTANDARD = LVCMOS33;
NET "port_led_n[7]" LOC = P64 | IOSTANDARD = LVCMOS33;
NET "port_led_n[8]" LOC = P66 | IOSTANDARD = LVCMOS33;
NET "port_led_n[9]" LOC = P68 | IOSTANDARD = LVCMOS33;

########################################################################################################################
# Expansion header SPI bus

NET "expansion_spi_miso" LOC = P18 | IOSTANDARD = LVCMOS33;
NET "expansion_spi_mosi" LOC = P19 | IOSTANDARD = LVCMOS33 | PULLUP;
NET "expansion_spi_sck"  LOC = P23 | IOSTANDARD = LVCMOS33 | PULLUP;
NET "expansion_spi_cs_n" LOC = P24 | IOSTANDARD = LVCMOS33 | PULLUP;

########################################################################################################################
# Clock

NET "clk_24mhz" LOC = P22 | IOSTANDARD = LVCMOS33;
NET "clk_24mhz" TNM_NET = "clk_24mhz";

# Disable timing analysis to remove warnings about not-found signals.
# We have no real logic anyway so there's no way we could fail timing
#TIMESPEC TS_clk_24mhz = PERIOD "clk_24mhz" 24 MHz HIGH 50 %;

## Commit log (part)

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2017-03-09 Removed trailing spaces
2017-03-09 Initial build script for nocbridge
2017-03-09 Commented out old nocbridge stuff as it's not yet usable
2017-03-09 Removed legacy tacoshield project
2017-03-09 nocbridge: Added types enum
2017-03-09 Continued initial nocswitch / NOCBridgeInterface work
2017-03-10 Continued initial implementation of JTAGNOCBridgeInterface
2017-03-10 Updated to latest bsps Added support for the nexys4ddr to the BlinkyTestBitstream
2017-03-17 Enable asan for debug builds
2017-03-17 nocswitch/nocbridge: Continued initial implementation of JTAGNOCBridgeInterface
2017-03-18 Continued work on JTAGNocBridgeInterface. Need to specify exact order of bytes going into checksum.
2017-03-20 Now verifying CRCs on inbound packets
2017-03-22 JTAGNOCBridgeInterface: continued work on processing incoming data. Now sending valid sequence numbers on outbound packets.
2017-03-23 old: Removed functions we already ported
2017-03-23 JTAGNOCBridgeInterface: Added test code to send an RPC message. Causes loss of sync, need to keep rx_buf and tx_buf across cycles
2017-03-24 JTAGNOCBridgeInterface: Fixed incorrect struct field ordering
2017-03-25 JTAGNOCBridgeInterface: Now computing outbound payload CRCs
2017-03-25 Initial checking of host-side CRCs from DUT payloads
2017-03-26 build: now keeping hierarchy by default
2017-03-30 Moved I2CTransceiver to ipcores
2017-03-30 PRBSTestBitstream: initial version
2017-03-30 nocswitch/nocbridge: Continued initial implementation. Can now send RPC messages from global FIFO to DUT, and print returned ones to console
2017-03-30 nocswitch: Continued cleanup and porting
2017-03-30 JtagBridgeTestBitstream: Now using RPCv3EchoNode instead of simple crossover wiring
2017-03-30 Removed more dead legacy code
2017-03-30 Removed obsolete legacy documentation
2017-03-30 Removed old legacy CMake file (wow, that's been sitting around for a while...)
2017-03-30 JtagBridgeTest: initial import from legacy
2017-03-30 Added new Splash build script for JtagBridgeTest
2017-03-31 JtagBridgeTest: Began refactoring
2017-03-31 NOCBridgeInterface: Added some prototypes for future functions
2017-04-01 JTAGNOCBridgeInterface: made AllocateClientAddress / FreeClientAddress thread safe
2017-04-01 nocbridge/nocswitch/JTAGBridgeTest: continued initial socket API work
2017-04-01 RPCMessage: Enabled Format()
2017-04-02 nocbridge/nocswitch: Initial RPC ping testing is now working over JTAG -> nocswitch
2017-04-02 Continued work on high speed PLL sampling
2017-04-03 PRBSTest: Bumped sample rate to 10 Gsps
2017-04-03 Updated to latest bsp
2017-04-04 Lots more work on PRBS testing, fixed numerous bugs
2017-04-08 Continued PRBS testing
2017-04-10 nocsim: Continued work on initial class hierarchy
2017-04-11 Moved IODelay* to ipcores
2017-04-11 Initial skeleton of GreenpakTimingTestBitstream
2017-04-12 nocsim: Added links between quadtree nodes
2017-04-13 nocsim: Can now render quadtree topology to SVG
2017-04-17 nocsim: Added CPU and RAM node types. Nodes now provide minimal responses when queried.
2017-04-17 Added more stats collection. Initial version of NIC.
2017-04-18 nocsim: Silenced some log messages. Now collecting latency stats on NoC
2017-04-18 nocsim: Added initial skeleton of GridRouter
2017-04-18 nocsim: Now creating edges between routers and hosts in grid topology
2017-04-19 nocsim: Initial implementation of grid router (X-Y only, no random yet) is working
2017-04-19 RPCv3TransceiverFormal: added named signals to unused ports to suppress Yosys warnings
2017-04-19 Refactoring: Broke RPCv3TransceiverFormal into four separate testbenches so we can run the tests for different data widths in parallel across multiple CPUs
2017-04-19 RPCv3TransceiverTest: added constraint for test harness
2017-04-20 Refactoring: renamed a bunch of directories and files for RPCv3Router tests
2017-04-22 Continued work on formal verification of SingleClockShiftRegisterFifo. All control-plane properties pass. Data plane is tricky to verify...
2017-04-23 Removed SMT constraints from ShiftRegisterFormal as they're no longer needed
2017-04-23 FifosFormal: Began work on proving correctness of FIFO
2017-04-23 FifosFormal: contiued fifo correctness proof
2017-04-24 Initial formal verification work on RPCv3RouterReceiver_collapsing. Not yet finished.
2017-04-25 Added 32/128 bit input tests for RPCv3RouterReceiver_collapsing. Completed initial verification work
2017-04-29 Added initial formal tests for RPCv3RouterReceiver_buffering
2017-05-01 RPCv3RouterReceiver tests now use RPCv3RouterReceiver instead of explicitly instantiating the various wrappers
2017-05-01 Fixed more paste bugs. Updated to latest ipcores
2017-05-02 RPCv3RouterTransmitter: began work on initial test skeleton
2017-05-03 TxRouterLinkTester: Continued adding constraints for valid input from router
2017-05-03 JtagPingTestBitstream / JtagPingTestBitstream_7series: Removed tests since they've been replaced by new stuff
2017-05-03 RPCv2EchoNodeWithDelay: removed as it's been replaced by newer code
2017-05-03 Udpated submodules
2017-05-05 Removed CoolRunner/crowbar stuff because this now lives in openfpga
2017-05-29 Updated library path
2017-05-29 Added JtagDebugBridge_addresses (new dependency) to all NoC tests. Updated GreenpakTimingTestBitstream for starshipraider board
2017-05-29 Continued initial work on Greenpak timing characterization tools
2017-05-31 Initial socket-ification of GreenpakTimingTest
2017-06-01 GreenpakTimingTest*: added support for more channels
2017-06-04 GreenpakTimingTest*: Improved flow control to allow pipelining
2017-06-05 Fixed bug where old messages would get interpreted as new ones due to not dropping redundant stuff
2017-06-05 GreenpakTimingTest*: disabled some debug reporting as it's not needed anymore
2017-06-07 Updated to latest xptools
2017-06-08 GreenpakTimingTest*: Moved inner characterization loop into FPGA
2017-06-10 Refactored GreenpakTimingTest to do rising/falling tests in one operation
2017-06-13 jtaghal: Updated to latest version
2017-07-06 Updated ignore properties
2017-07-10 Updating PRBS test to STARSHIPRAIDER RAM bus
2017-07-21 Initial control code for temp sensor on GreenPAK thermal characterization board
2017-07-26 Moved Oscilloscope out of legacy
2017-07-26 Continued initial porting to new exception setup
2017-07-26 Continued porting. Cleaned up OscilloscopeChannel
2017-07-26 Initial import of OscilloscopeSample
2017-07-26 Initial import of legacy RED TIN, disabled all of the NoC stuff we don't support in v3 yet
2017-07-27 Moved UART core to ipcores
2017-07-27 nocswitch: Detect when socket is closed. Fixes #3.
2017-07-27 Continued initial RED TIN UART bring-up. Can now load channel descriptor ROMs and configure everything, but not actually trigger or capture.
2017-08-01 Continued work on data capture for LA
2017-08-01 Moved scopeclient out of legacy
2017-08-01 Removed legacy Splashfile
2017-08-01 Fixed indentation
2017-08-01 Moved TimescaleRenderer out of legacy
2017-08-01 Various improvements to scopeclient
2017-08-03 Removed Vivado memory corruption workarounds. We now detect buggy ROMs, print a warning message with the workaround, and abort.
2017-09-30 AnalogRenderer: removed trailing spaces
2017-09-30 Initial import/cleanup of protocol decoder base class
2017-10-01 VICP: Added better progress reporting when downloading large captures
2017-10-02 Fixed timescale rendering
2017-10-02 Moved TextRenderer out of legacy
2017-10-02 CaptureChannel: made a bunch of functions const
2017-10-02 Ethernet decoder/renderer now support checksum and Ethertype properly
2017-10-03 Moved AsciiRenderer out of legacy
2017-10-03 Moved UARTDecoder out of legacy
2017-10-03 Implemented support for multiple protocol chained decoders
2017-10-03 scopeclient now uses mouse wheel for timescale adjustments, removed zoom buttons from toolbar
2017-10-07 LeCroyVICPOscilloscope now supports MSO channels.
2017-10-09 Refactoring: moved Ethernet frame reassembly from bytes into its own class. Added skeleton for 100baseT decoder.
2017-10-13 Fixed LFSR sync for 100baseTX decoder
2017-10-13 Initial eye rendering is kinda working. Hard-codes lots of settings still.
2017-10-14 Quick culling of out-of-range samples in ChannelRenderer
2017-10-14 Performance fixes to timescale rendering
2017-10-15 EyeDecoder: correctly set channel type
2017-10-15 Added vertical zoom control
2017-10-15 Added horizontal grid support. No text labels yet.
2017-10-15 Eye renderer now uses Y axis grid rendering from AnalogRenderer
2017-10-16 Time scale now renders with double precision to avoid roundoff errors with long captures
2017-10-16 Initial version of Ethernet autonegotiation decoder
2017-10-18 Improved support for segmented capture
2017-10-18 Fixed sign bug in offset calculation
2017-10-18 AnalogRenderer: moved PickStepSize into a static function
2017-10-19 Eye rendering: Added color ramp legend
2017-10-19 Major refactoring of eye rendering into separate functions. A few additional display improvements.
2017-10-20 Much more accurate calculation of symbol rate, various UI tweaks to eye renderer
2017-10-21 Added instrument type detection and DVM detection. No actual DVM UI implemented yet.
2017-10-21 Implemented DMM mode for WS3K. So far stuck at DC voltage and whatever channel was selected when the scope was turned on.
2017-10-21 Implemented meter enable/disable and autoranging
2017-10-22 Initial TRAGICLASER PRBS firmware
2017-10-22 Fixed unused-argument warning
2017-10-22 Initial implementation of pseudo-differential protocol decoder
2017-10-22 Eye analysis now includes rise/fall times (10-90%)
2017-10-22 Ethernet100BaseTDecoder: Fixed crash when we fail to sync RX LFSR
2017-10-22 Lots more work on TRAGICLASER PHY. Can now send valid preamble, SSD, ESD. No actual MII interface yet.
2017-10-23 VICP oscilloscope now checks which channels are enabled and doesn't show those that aren't on. Fixed a bunch of crashes related to invisible channels.
2017-10-30 Fixed a few bugs causing crashes when CH1 was disabled
2017-11-01 SPI flash test now works (some of the time!)
2017-11-13 Lots more work on TRAGICLASER TX. Added pre-emphasis for much nicer TX waveforms
2017-11-14 Initial work on TRAGICLASER RX
2017-11-16 Finished initial version of PSU UI
2017-11-17 Fixed old debug code
2017-11-17 Continued debugging TRAGICLASER PHY. RX side now can correctly recover scrambled 5-bit data blocks with unknown word and LFSR sync.
2017-11-18 TRAGICLASER: Initial RX LFSR alignment is tested and working
2017-11-19 Finished 100Mbit PHY RX side, all the way to MII interface
2017-11-20 scopeprotocols: Improvements to eye decoder for weird duty cycles
2017-11-21 Timing improvements to I/O buffer block
2017-11-21 Added traffic activity LED. Fixed bug causing false "0" bits to be inserted around slow-rise-time pulses
2017-11-25 Removed some dead code causing warnings
2018-02-27 Moved EthernetMDIOTransceiver to ipcores repo
2018-03-05 Moved a bnuch of apps to jtaghal-apps
2018-03-24 InternetChecksum: moved to ipcores
2018-05-01 MARBLEWALRUS: converted old files to new kicad
2018-05-01 Initial graph support for PSU controls
2018-05-04 EyeDecoder: Fixed rise/fall time being incorrect in some cases when we didn't have an edge at the expected time
2018-05-04 Updated paths for resource usage estimate
2018-07-04 TRAGICLASER: Added support for sending closely spaced FLPs for EMC testing
2018-07-04 Various fixes for capture timing etc
2018-10-13 Removed EthernetBusWidthConvertr (replaced by modern PLL-based version in antikernel-ipcores)
2019-07-08 converted for recent-ish kicad
2019-07-08 Added X25519 unit tests
2019-07-18 Initial implementation of x25519_freeze + test
2019-07-19 Finished multiplication tests
2019-08-18 Updated to latest ipcores, moved OnDieSensors_7series to ipcores
2019-09-11 Removed autogenerated files
2019-09-15 Removed Mult121665
2019-09-25 Continued testing x25519
2019-10-09 Initial test case for StreamingHMACSHA256
2019-10-11 Implemented second RFC4231 test vector
2019-12-03 StreamingSHA256Test: fixed bug causing incorrect length in most recent test case
2020-04-23 Removed never-implemented MARBLEWALRUS JTAG
2020-04-23 Removed old Flying Crowbar sandbox
